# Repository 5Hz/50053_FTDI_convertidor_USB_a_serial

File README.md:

Tarjeta FTDI (convertidor usb - serial) para Arduino - 5V
=========================================================

Esta tarjeta contiene un FTDI FT232RL para conversión USB a serial. El pinout de esta tarjeta es idéntico al de un cable FTDI para trabajar con tarjetas Arduino a 5V. Así mismo posee un jumper para configurarla a 3.3V o 5V tanto en niveles de alimentación como en I/O.

Para mas informacion puedes visitar la [**pagina del producto**](http://5hertz.com/index.php?main_page=product_info&cPath=67_68_130&products_id=470).

Contenidos del repositorio
--------------------------
Aqui puedes encontrar los archivos fuente de este dispositivo ordenados de la siguiente manera:

- **/Eagle** Archivos de diseño en Eagle (.brd, .sch)
- **/Arduino** Librerias y codigos ejemplo.

Informacion de la licencia
-------------------

* El hardware esta publicado bajo la licencia [Creative Commons Share-alike 3.0](http://creativecommons.org/licenses/by-sa/3.0/).
* Todo el contenido adicional es de *codigo abierto* *(open source)*, ten la libertad para utilizarlo como quieras.

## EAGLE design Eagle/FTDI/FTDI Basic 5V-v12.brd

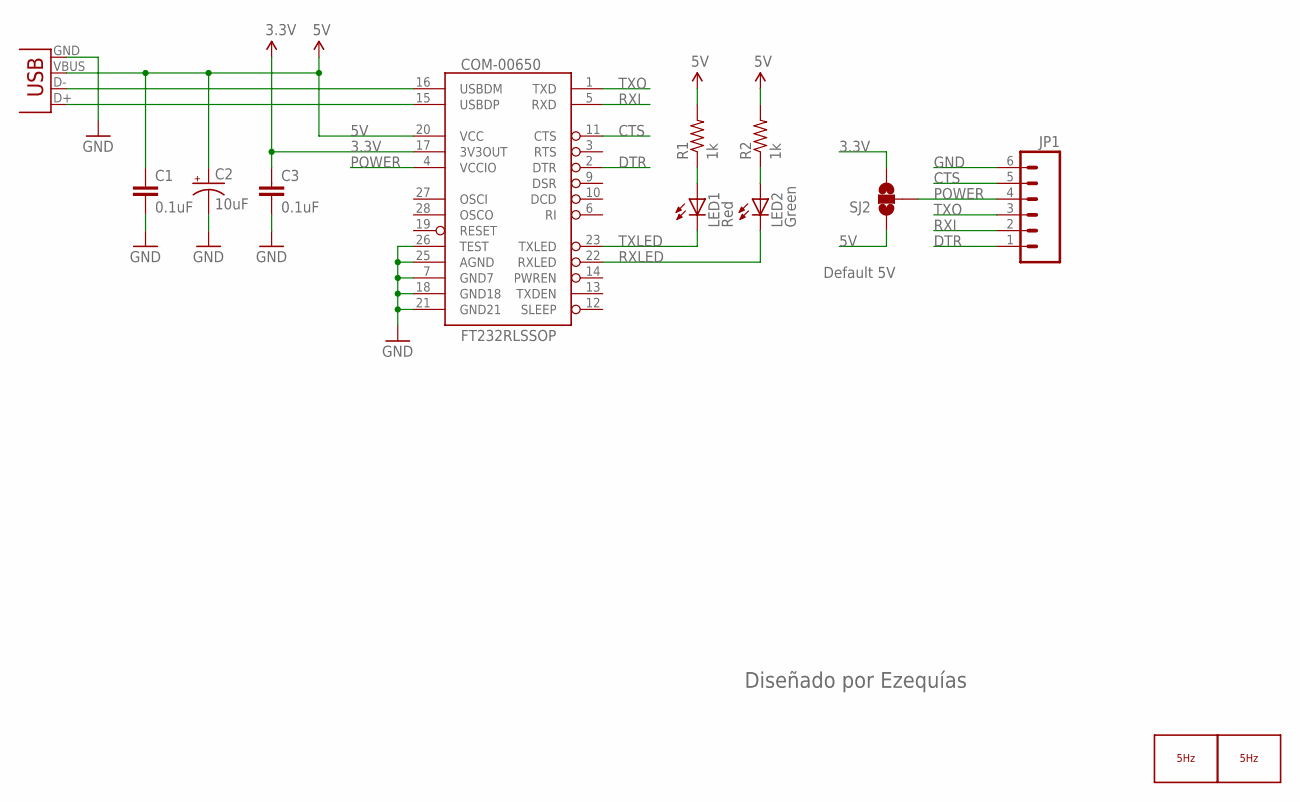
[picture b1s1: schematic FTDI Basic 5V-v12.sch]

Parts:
C1, C3: 0.1uF; 0603-CAP
C2: 10uF; EIA3216
COM-00650: FT232RLSSOP; SSOP28DB
JP1: M06SIP; 1X06
LED1: Red; LED-0603
LED2: Green; LED-0603
LOGO1: LOGO_5HZ_H_5MM; 5HZ_LOGO_H_5MM
LOGO2: LOGO_5HZ_H_15MM; 5HZ_LOGO_H_15MM
PRT-00587: 897-43-005-00-100001; USB-MINIB
R1, R2: 1k; 0603-RES
SJ2: SOLDERJUMPER_2WAYS; SJ_3

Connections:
3.3V: C3.1, COM-00650.17 (3V3OUT), SJ2.3
5V: C1.1, C2.A (+), COM-00650.20 (VCC), PRT-00587.VBUS, R1.2, R2.2, SJ2.1
CTS: COM-00650.11 (CTS), JP1.5
DTR: COM-00650.2 (DTR), JP1.1
GND: C1.2, C2.C (-), C3.2, COM-00650.7 (GND7), COM-00650.18 (GND18), COM-00650.21 (GND21), COM-00650.25 (AGND), COM-00650.26 (TEST), JP1.6, PRT-00587.GND
unnamed: LED1.A, R1.1
unnamed: LED2.A, R2.1
POWER: COM-00650.4 (VCCIO), JP1.4, SJ2.2
RXI: COM-00650.5 (RXD), JP1.2
RXLED: COM-00650.22 (RXLED), LED2.C
TXLED: COM-00650.23 (TXLED), LED1.C
TXO: COM-00650.1 (TXD), JP1.3
USB_D+: COM-00650.15 (USBDP), PRT-00587.D+
USB_D-: COM-00650.16 (USBDM), PRT-00587.D-

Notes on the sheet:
Default 5V
Diseñado por Ezequías

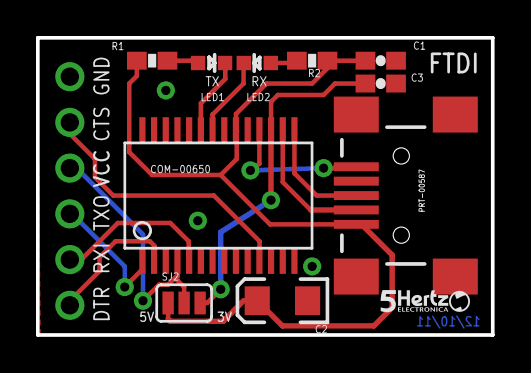
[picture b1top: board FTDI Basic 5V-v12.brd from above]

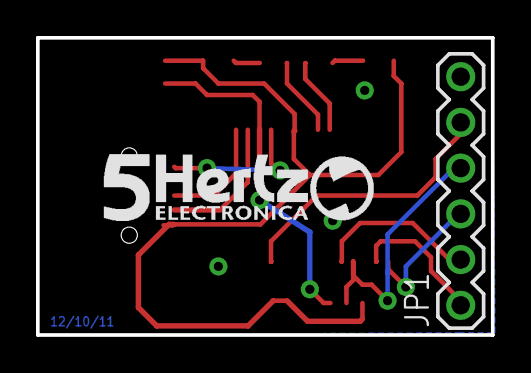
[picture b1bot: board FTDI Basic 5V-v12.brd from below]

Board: 2 copper layers, 25.3 x 16.5 mm, 13 parts (2 on the bottom side), 14 nets.

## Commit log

2014-01-13 creación
2014-01-21 Foto del producto
